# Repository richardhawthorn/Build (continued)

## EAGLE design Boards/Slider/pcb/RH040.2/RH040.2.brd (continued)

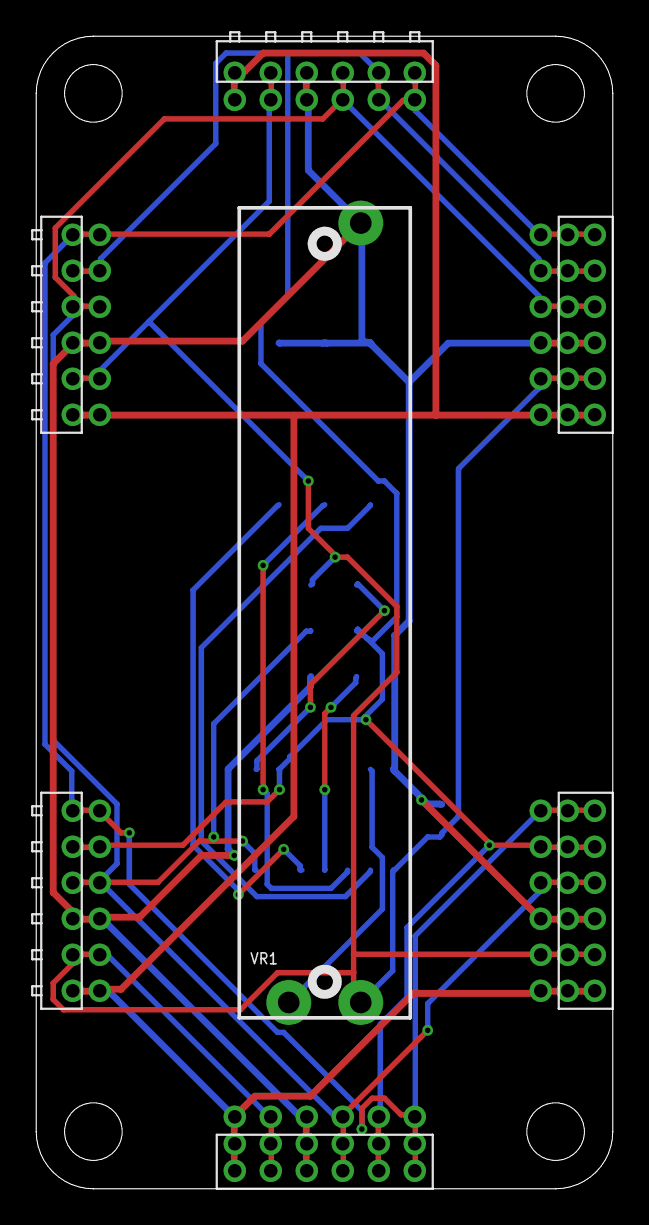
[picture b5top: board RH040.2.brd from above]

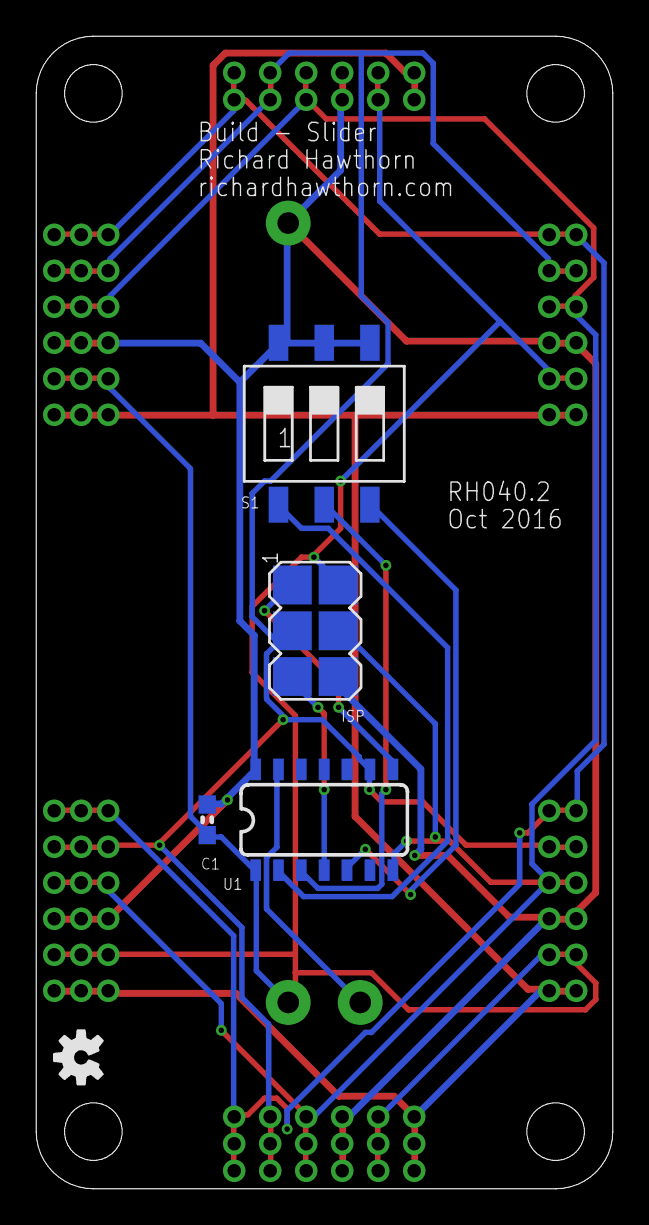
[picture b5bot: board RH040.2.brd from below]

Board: 2 copper layers, 32.0 x 64.0 mm, 12 parts (5 on the bottom side), 12 nets.

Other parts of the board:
U$3: OSHW-LOGO-S
